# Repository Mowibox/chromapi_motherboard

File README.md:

# chromapi_motherboard

This repo contains a dedicated control HAT designed to manage the high-speed motion, power distribution, and sensor integration required for the quadruped robot [Chromapi](https://github.com/Mowibox/chromapi).

*Designed with KiCad 10.*

## Table of contents

| Section | Description |
| --- | --- |
| [Project overview](#project-overview) | General description of the quadruped control board |
| [Authors](#authors) | Main contributors information |
| [Sponsors & Acknowledgements](#sponsors--acknowledgements) | Information about project sponsors and hardware support |
| [Resources & Documentation](#resources--documentation) | Links to datasheets, BOM, and design architectures |
| [Contributions](#contributions) | How to contribute to the repository |
| [License](#license) | Licensing information |

## Project overview

| Resource | Description | Location | Status |
| :--- | :--- | :--- | :--- |
| **💻 Firmware** | STM32 low-level drivers and communication protocol. | [`/firmware`](./firmware) | **Available** |
| **📐 Schematics** | PDF for hardware architecture | [`/hardware/schematic_pdf`](./hardware/schematic_pdf/chromapi_motherboard_v1.pdf) | **Available** |
| **📦 Manufacturing** | Gerbers, Drill files, BOM, and CPL for assembly. | [`/hardware/production`](./hardware/production/) | **Available** |

### Chromapi's Anatomy

* **🧠 The Brain**: The STM32G431KBT6 MCU handles real-time tasks: servo control, IMU fusion, and power monitoring. The Raspberry Pi runs high-level control, vision, and the Python SDK. They communicate through a custom UART bridge at 2 Mbps.

* **💪 The Muscles**: The SN74LVC1G126 and SN74LVC1G125 buffer the half-duplex TTL serial bus (a single data wire, its direction switched by the USART hardware DE signal) for 12 Feetech STS3215 servos. The STM32 polls servo positions at 200 Hz.

* **❤️ The Heart**: The TPS51388 converts the 18650 2S battery voltage to 5V. The LD39050 generates the 3.3V rail. The INA226 monitors voltage, current, and power via I2C.

* **🛡️ The Immune System**: The CN3302 charges the two 18650 Li-ion cells through USB-C. The HY2120 provides protection against over-discharge, over-current, and short circuits.

* **👁️ The Senses & Balance**: The BMI088 IMU gives acceleration and angular velocity data with SPI. A Mahony filter runs at 400 Hz and outputs orientation as a quaternion. Four foot switches detect ground contact for gait timing.

* **🗣️ The Voice & Expression**: The MAX98357A drives the speaker via I2S communication. The ICS-43434 microphone captures audio through I2S. And the SN74AHCT1G125 level-shifts the 3.3V signal to 5V for the WS2812B RGB LEDs.

## Authors

| |
| :---: |
|  |
| [**Ousmane THIONGANE**](https://mowibox.github.io) |

## Sponsors & Acknowledgements

The hardware development of this board relies on the resources provided by the sponsors below.

### PCBWay

**[PCBWay](https://www.pcbway.com)** is a global manufacturer specializing in rapid prototyping and low-volume hardware production, offering advanced PCB fabrication, turnkey assembly, CNC machining, and 3D printing.

<p align="center">
  
</p>

For this project, I utilized their sponsored [PCB manufacturing](https://www.pcbway.com/orderonline.aspx) and [assembly](https://www.pcbway.fr/pcb-assembly.html) (PCBA) services. Beyond fast production, their engineering team excels at detailed file reviews by cross-checking design options, BOMs, and footprints to prevent errors early. Their reliable component sourcing and rigorous verification were of great help in building a high-quality prototype for Chromapi's motherboard.

---

> Huge thanks to all the hardware folks who reviewed my schematics, or gave me layout tips. I really appreciate your time and support!

## Resources & Documentation

| **⚡ Specifications** | **📄 Bill of Materials** | **📡 Protocol Reference** |
| :---: | :---: | :---: |
| Operating voltages, current limits, and thermal ratings. | Detailed BOM with part numbers and unit costs. | Custom UART protocol between RPi and STM32. |
| 👉 [**View Specs**](https://mowibox.github.io/chroma/en/chromapi/specifications/general/) | 👉 [**View BOM**](https://mowibox.github.io/chroma/en/chromapi/bom/pcb_bom/) | 👉 [**View Protocol**](https://mowibox.github.io/chroma/en/chromapi/documentation/protocol/) |

### Power Architecture

```mermaid
%%{init: {'themeCSS': '.edgeLabel, .edgeLabel p, .labelBkg { background-color: transparent !important; } .edgeLabel rect { fill: transparent !important; }'}}%%
flowchart TD
    CHG[["USB-C charge<br/>CN3302"]] -.->|"charge → B+ ≈ 7.2–8.4V"| CELLS[("Battery<br/>18650 x2")]
    CELLS -->|"B+/BM/B-"| HY["HY2120<br/>BMS protection"]
    HY -->|"B+"| SW[["Power switch"]]

    SW -->|"V_BATT ≈ 7.2–8.4V"| SHUNT[["INA226 shunt sense<br/>2mΩ"]]
    SHUNT -->|"V_SYS ≈ 7.2–8.4V"| REG5{{"Voltage regulation<br/>TPS51388 · Fsw=600kHz"}}
    SHUNT -->|"V_SYS"| SERVOS(["Servomotors x12<br/>Feetech STS3215-C001"])

    REG5 -->|"+5V"| RPI["Raspberry Pi"]
    REG5 -->|"+5V"| FANPWR(["Fan<br/>Noctua NF-A4x10"])
    REG5 -->|"+5V"| LEDPWR(["RGB LEDs<br/>WS2812B"])
    REG5 -->|"+5V"| REG33{{"Voltage regulation<br/>LD39050 LDO"}}

    REG33 -->|"+3.3V"| MCU["MCU<br/>STM32G431KBT6"]
    REG33 -->|"+3.3V"| IMU["IMU<br/>BMI088"]
    REG33 -->|"+3.3V"| INA["Power monitor<br/>INA226"]
    REG33 -->|"+3.3V"| AUDIO["Speaker + Microphone<br/>MAX98357A / ICS-43434"]

    classDef power fill:#dd2757,color:#ffffff,stroke:none
    classDef voltreg fill:#ea684c,color:#ffffff,stroke:none
    classDef ic fill:#25b3ae,color:#ffffff,stroke:none
    classDef actuator fill:#c027e7,color:#ffffff,stroke:none
    classDef sensor fill:#5c5aed,color:#ffffff,stroke:none

    class CHG,CELLS,HY,SW power
    class REG5,REG33 voltreg
    class MCU,RPI,AUDIO ic
    class SERVOS,FANPWR,LEDPWR actuator
    class SHUNT,IMU,INA sensor
```

### Communication Architecture

```mermaid
%%{init: {'themeCSS': '.edgeLabel, .edgeLabel p, .labelBkg { background-color: transparent !important; } .edgeLabel rect { fill: transparent !important; }'}}%%
flowchart LR
    RPI["Raspberry Pi"]
    MCU["STM32G431KBT6<br/>SYSCLK · 160 MHz"]
    SERVOS(["Servomotors x12<br/>STS3215-C001"])
    IMU["IMU<br/>BMI088"]
    PWR["Power Monitor<br/>INA226"]
    LED(["RGB LEDs<br/>WS2812B"])
    CAM["Wide Angle Camera<br/>IMX219-D160"]
    AUDIO["Speaker + Microphone<br/>MAX98357A / ICS-43434"]
    FAN(["Fan<br/>Noctua NF-A4x10"])

    RPI <-->|"Custom bridge protocol<br/>UART1 · 2 Mbps · 100 Hz control loop"| MCU
    MCU <-->|"Half-duplex serial<br/>USART2 · 1 Mbps · 200 Hz"| SERVOS
    MCU <-->|"SPI1 · 5 MHz · 400 Hz (Mahony AHRS)"| IMU
    MCU <-->|"I2C1 · 400 kHz · 10 Hz poll"| PWR
    MCU -->|"PWM+DMA · 800 kHz"| LED

    RPI -->|"CSI-2"| CAM
    RPI <-->|"I2S"| AUDIO
    RPI <-->|"PWM + Tacho"| FAN

    classDef ic fill:#25b3ae,color:#ffffff,stroke:none
    classDef actuator fill:#c027e7,color:#ffffff,stroke:none
    classDef sensor fill:#5c5aed,color:#ffffff,stroke:none

    class RPI,MCU,AUDIO ic
    class SERVOS,LED,FAN actuator
    class IMU,PWR,CAM sensor
```

## Contributions

Contributions are always welcome!

* **Report Issues:** Found an error or have a feature request? Create a new issue [here.](https://github.com/Mowibox/chromapi_motherboard/issues/new/choose)
* **Fix Bugs & Add Features:** Find out where you can lend a hand by checking out [existing issues.](https://github.com/Mowibox/chromapi_motherboard/issues)

## License

This repository is multi-licensed:

| Part | Path | License |
| :--- | :--- | :--- |
| Firmware (own code) | [`/firmware`](./firmware/) | [Apache 2.0](./LICENSE) |
| Hardware (schematics, PCB, footprints, symbols, fabrication files) | [`/hardware`](./hardware/) | [CC BY-NC-SA 4.0](./hardware/LICENSE) |
| Documentation and media (README, images, renders) | [`/assets`](./assets/), this README | [CC BY-NC-SA 4.0](./hardware/LICENSE) |

**Third-party content keeps its own license:** the STM32G4 HAL and CMSIS in [`/firmware/chromapi_stm32_core/Drivers`](./firmware/chromapi_stm32_core/Drivers/) (see their `LICENSE.txt`) and STM32CubeMX-generated files (`main.c`, `stm32g4xx_*`, `syscalls.c`, `sysmem.c`, `system_stm32g4xx.c`, startup and linker files) belong to STMicroelectronics; `ina226.[ch]` is Apache 2.0 by AutoFox; `bmi088.[ch]` is adapted from [pms67/LittleBrain-STM32F4-Sensorboard](https://github.com/pms67/LittleBrain-STM32F4-Sensorboard) and `ws2812b.[ch]` from [hey-frnk/STM32_HAL_NeoPixel](https://github.com/hey-frnk/STM32_HAL_NeoPixel); datasheets in [`/docs`](./docs/) and 3D models in [`/hardware/3d_models`](./hardware/3d_models/) belong to their respective manufacturers; the PCBWay logo (`assets/pcbway.png`) belongs to PCBWay.

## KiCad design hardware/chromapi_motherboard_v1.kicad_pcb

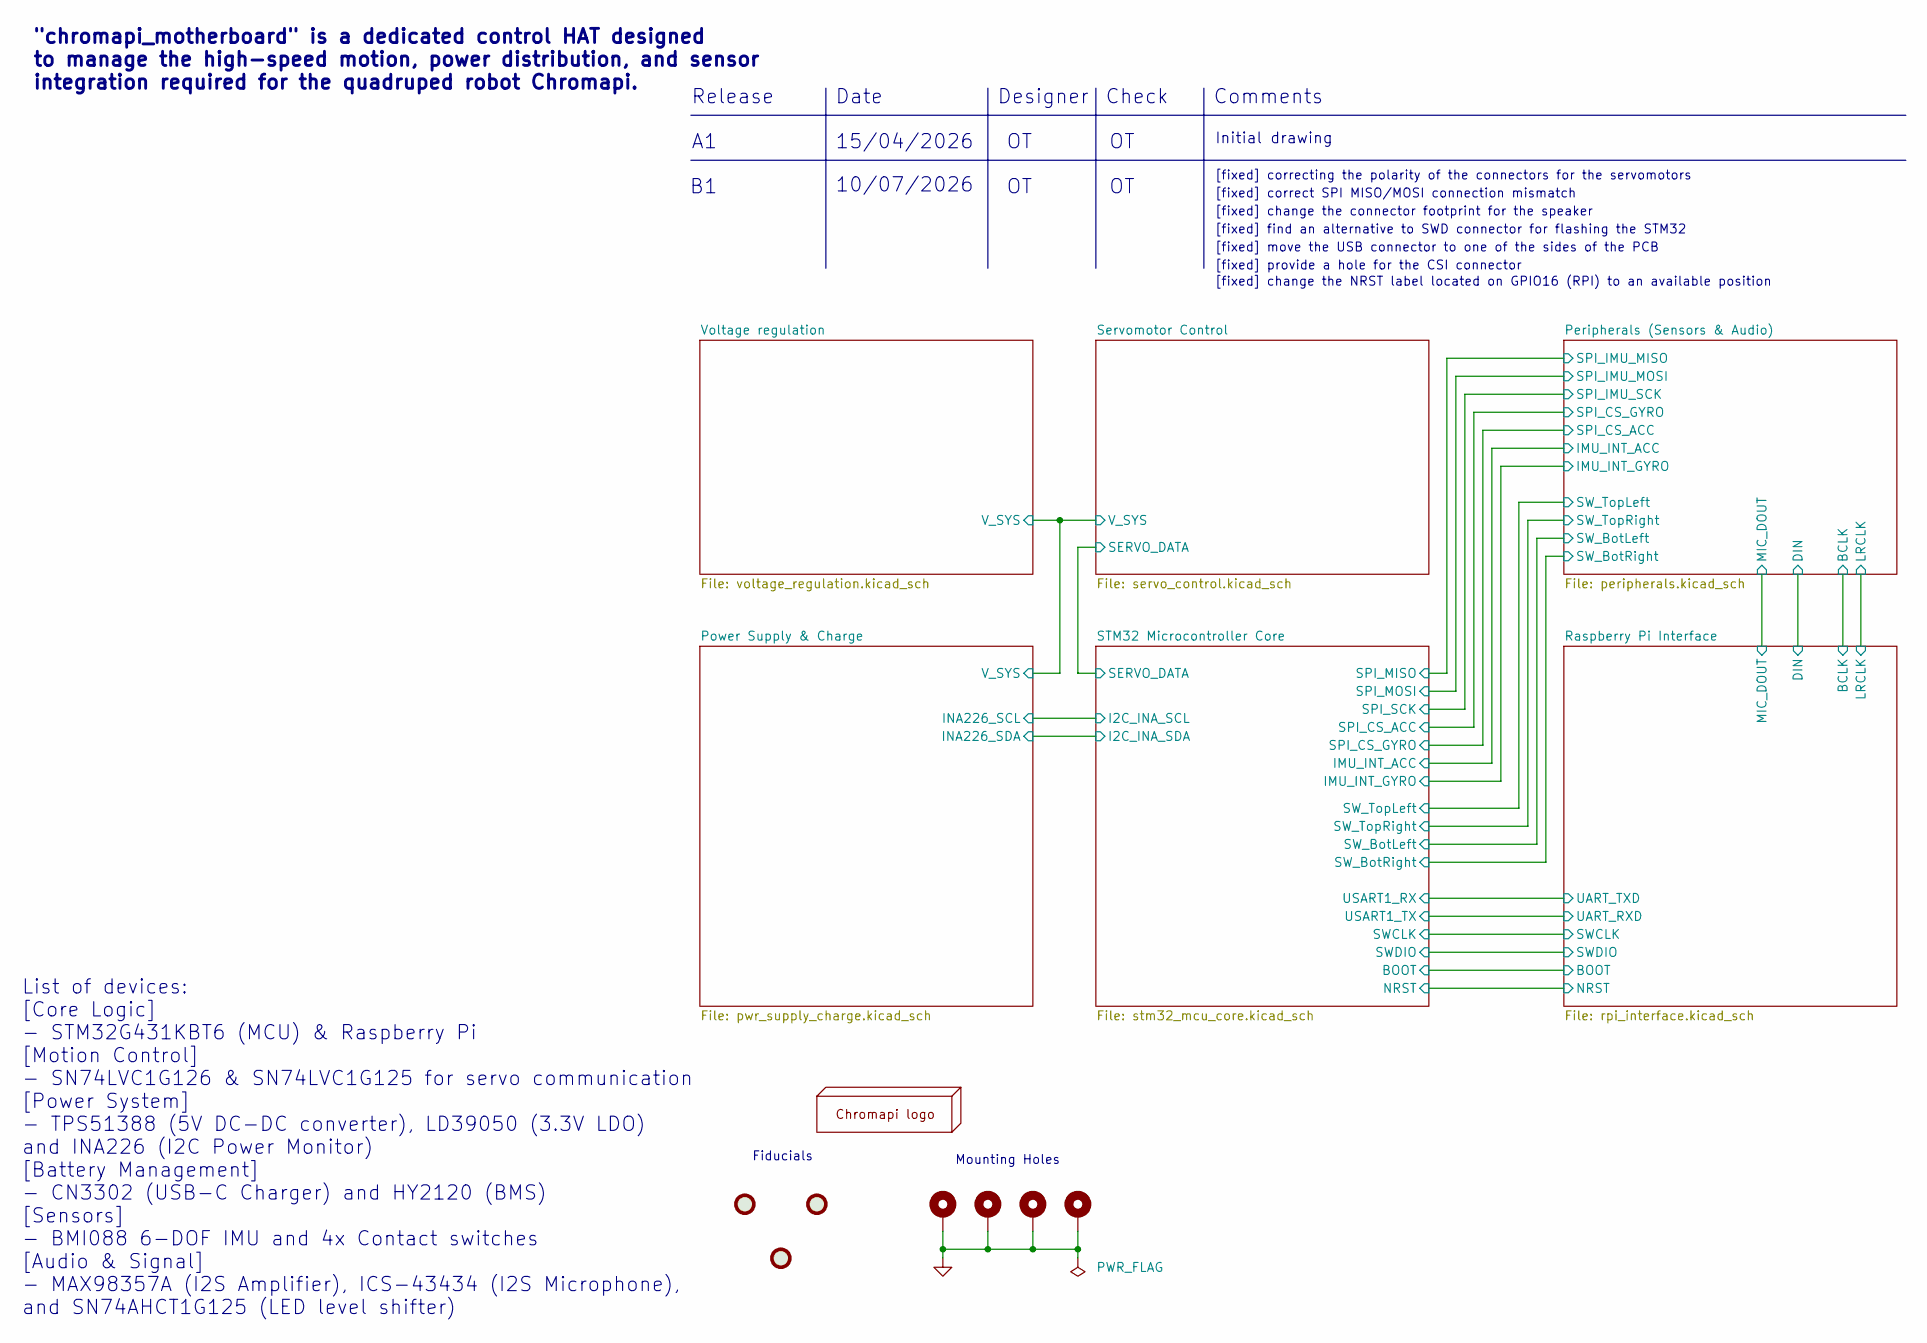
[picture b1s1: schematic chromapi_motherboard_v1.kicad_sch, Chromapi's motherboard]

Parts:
FID1, FID2, FID3: Fiducial; Fiducial_1mm_Mask2mm
H1: chromapi_logo
H2, H3, H4, H5: MountingHole_Pad; MountingHole_2.7mm_M2.5_Pad_Via

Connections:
GND: H2.1 (1_1), H3.1 (1_1), H4.1 (1_1), H5.1 (1_1); also elsewhere on the board

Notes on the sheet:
[fixed] change the connector footprint for the speaker
[fixed] change the NRST label located on GPIO16 (RPI) to an available position
Check
[fixed] correcting the polarity of the connectors for the servomotors
[fixed] provide a hole for the CSI connector
Initial drawing
Release
10/07/2026
[fixed] move the USB connector to one of the sides of the PCB
[fixed] find an alternative to SWD connector for flashing the STM32
"chromapi_motherboard" is a dedicated control HAT designed to manage the high-speed motion, power distribution, and sensor integration required for the quadruped robot Chromapi.
Date
List of devices: [Core Logic] - STM32G431KBT6 (MCU) & Raspberry Pi [Motion Control] - SN74LVC1G126 & SN74LVC1G125 for servo communication [Power System] - TPS51388 (5V DC-DC converter), LD39050 (3.3V LDO) and INA226 (I2C Power Monitor) [Battery Management] - CN3302 (USB-C Charger) and HY2120 (BMS) 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
Fiducials
15/04/2026
Comments
Designer
Mounting Holes
[fixed] correct SPI MISO/MOSI connection mismatch

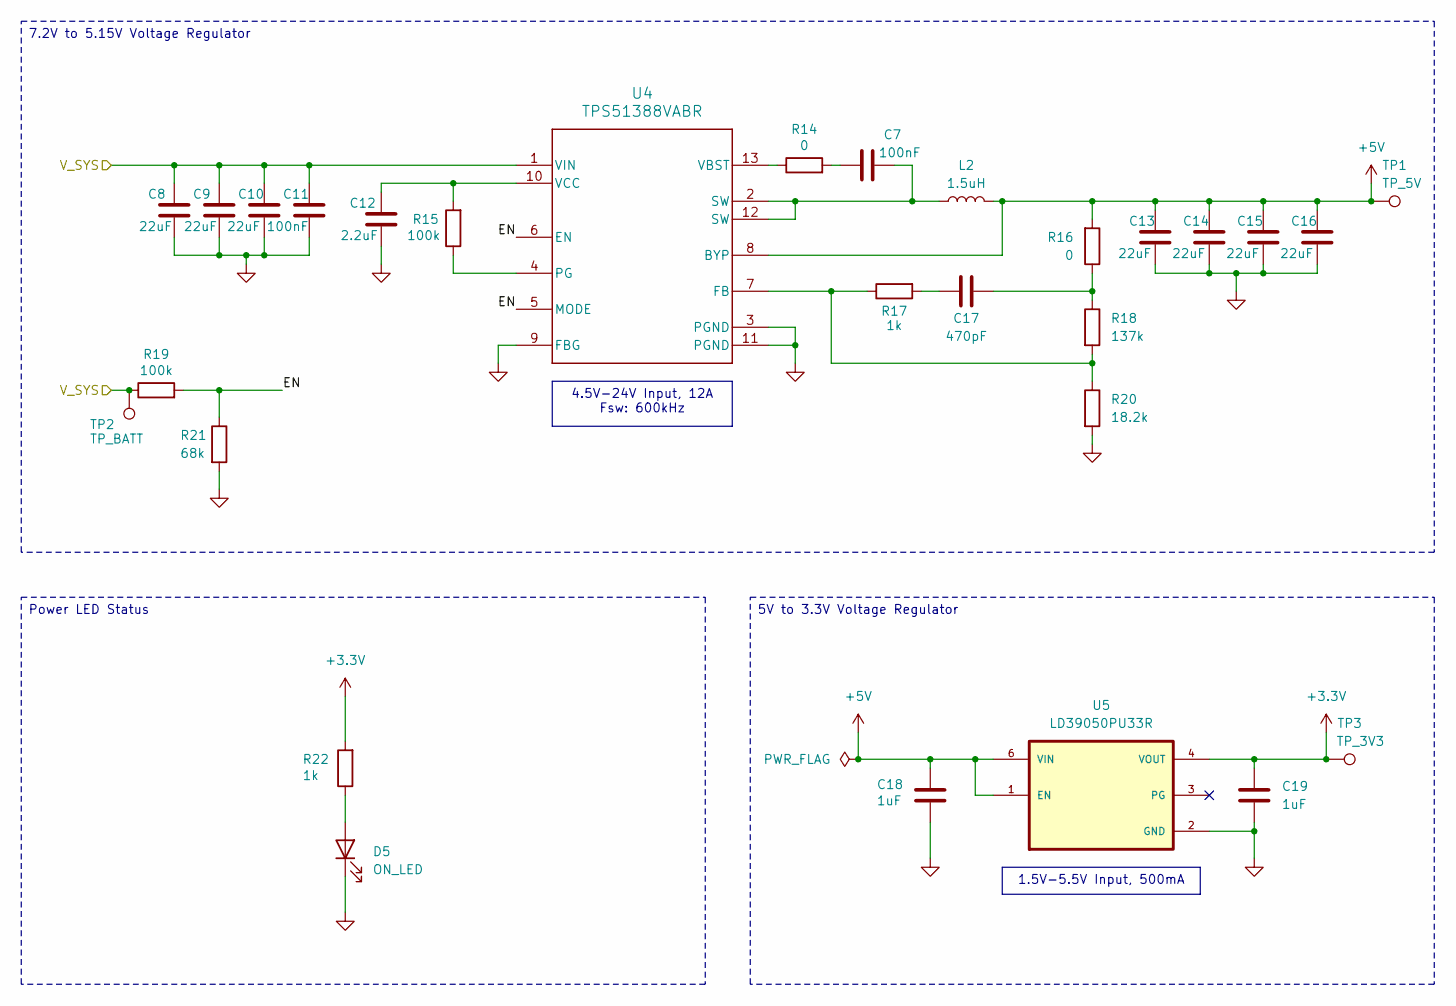
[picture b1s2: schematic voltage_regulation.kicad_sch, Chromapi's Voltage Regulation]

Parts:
C7: 100nF; C_0603_1608Metric; MPN CL10B104KB8NNNC; JLCPCB Part # C14663
C8, C9, C10: 22uF; C_1206_3216Metric; MPN CL31A226KAHNNNE; JLCPCB Part # C12891
C11: 100nF; C_0603_1608Metric; MPN CC0603KRX7R9BB104; JLCPCB Part # C14663
C12: 2.2uF; C_0603_1608Metric; MPN CL10A225KO8NNNC; JLCPCB Part # C23630
C13, C14, C15, C16: 22uF; C_0805_2012Metric; MPN CL21A226MAQNNNE; JLCPCB Part # C45783
C17: 470pF; C_0603_1608Metric; MPN CC0603JRNPO9BN471; JLCPCB Part # C106211
C18, C19: 1uF; C_0603_1608Metric; MPN CL10A105KB8NNNC; JLCPCB Part # C15849
D5: ON_LED; LED_0603_1608Metric; MPN KT-0603B; JLCPCB Part # C2288
L2: 1.5uH; IND_1040-WE-HCI_WRE; MPN 7443552150; JLCPCB Part # C5914133
R14, R16: 0; R_0603_1608Metric; MPN 0603WAF0000T5E; JLCPCB Part # C21189
R15, R19: 100k; R_0603_1608Metric; MPN CRCW0603100KFKEA; JLCPCB Part # C844916
R17, R22: 1k; R_0603_1608Metric; MPN 0603WAF1001T5E; JLCPCB Part # C21190
R18: 137k; R_0603_1608Metric; MPN 0603WAF1373T5E; JLCPCB Part # C22872
R20: 18.2k; R_0603_1608Metric; MPN RC0603FR-0718K2L; JLCPCB Part # C137784
R21: 68k; R_0603_1608Metric; MPN CRCW060368K0FKEA; JLCPCB Part # C844803
TP1: TP_5V; TestPoint_Pad_D1.5mm
TP2: TP_BATT; TestPoint_Pad_D1.5mm
TP3: TP_3V3; TestPoint_Pad_D1.5mm
U4: TPS51388VABR; TPS513885VABR; MPN TPS513885VABR; JLCPCB Part # C41935536
U5: LD39050PU33R; ld39050PU33R_SON95P300X300X100-7N; MPN LD39050PU33R; DIGI-KEY_PART_NUMBER 497-8716-1-ND

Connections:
+3.3V: C19.1, R22.2, TP3.1 (1_1), U5.4 (VOUT); also elsewhere on the board
+5V: C13.1, C14.1, C15.1, C16.1, C18.1, L2.2, R16.2, TP1.1 (1_1), U4.8 (BYP), U5.1 (EN), U5.6 (VIN); also elsewhere on the board
/Power Supply & Charge/V_SYS: C8.1, C9.1, C10.1, C11.1, R19.1, TP2.1 (1_1), U4.1 (VIN); also elsewhere on the board
/Voltage regulation/EN: R19.2, R21.1, U4.5 (MODE), U4.6 (EN)
GND: C8.2, C9.2, C10.2, C11.2, C12.2, C13.2, C14.2, C15.2, C16.2, C18.2, C19.2, D5.1 (K), R20.2, R21.2, U4.3 (PGND), U4.9 (FBG), U4.11 (PGND), U5.2 (GND), U5.7 (GND); also elsewhere on the board
unnamed: C7.1, L2.1, U4.2 (SW), U4.12 (SW)
unnamed: C7.2, R14.2
unnamed: C17.1, R16.1, R18.1
unnamed: C17.2, R17.2
unnamed: D5.2 (A), R22.1
unnamed: R17.1, R18.2, R20.1, U4.7 (FB)
unnamed: R15.1, U4.4 (PG)
unnamed: R14.1, U4.13 (VBST)
unnamed: C12.1, R15.2, U4.10 (VCC)

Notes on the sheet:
Power LED Status
4.5V-24V Input, 12A Fsw: 600kHz
5V to 3.3V Voltage Regulator
1.5V-5.5V Input, 500mA
7.2V to 5.15V Voltage Regulator

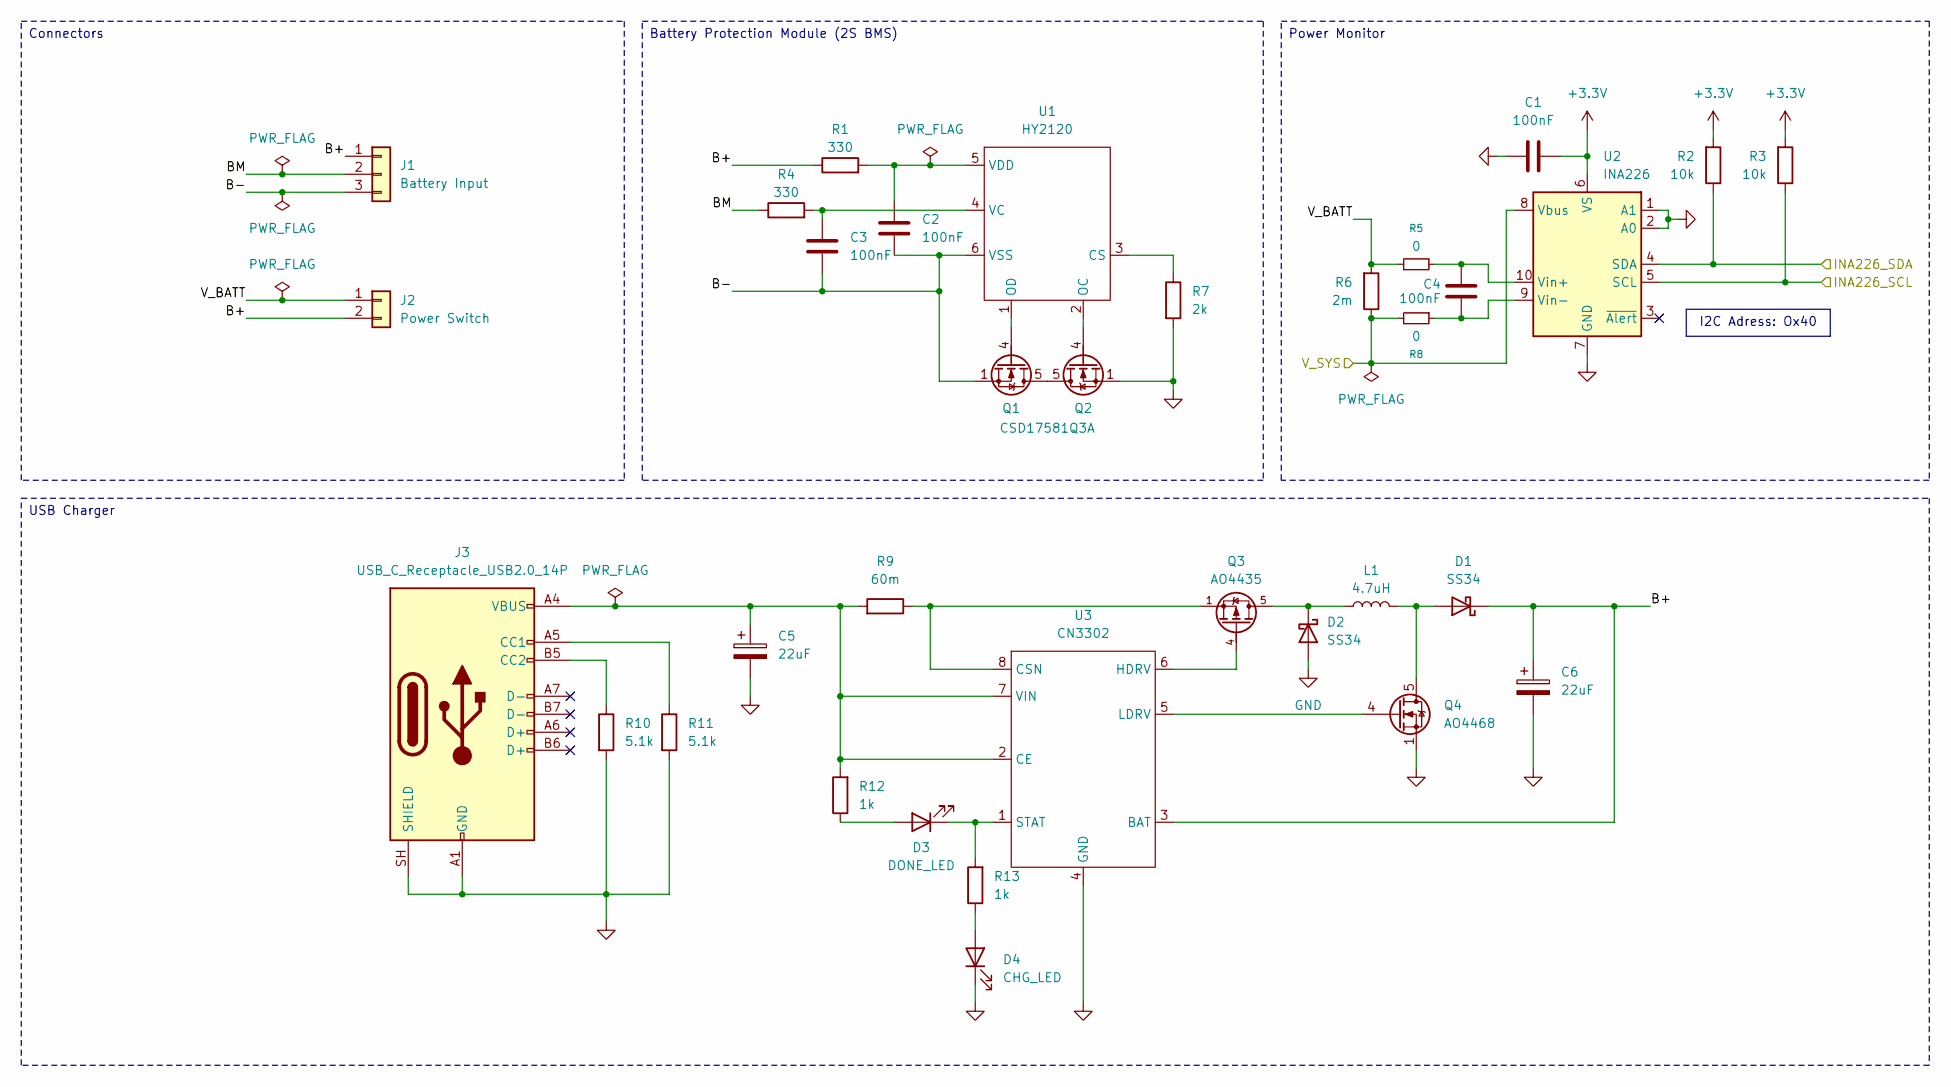
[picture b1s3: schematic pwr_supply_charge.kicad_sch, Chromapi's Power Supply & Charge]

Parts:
C1, C4: 100nF; C_0603_1608Metric; MPN CC0603KRX7R9BB104; JLCPCB Part # C14663
C2, C3: 100nF; C_0402_1005Metric; MPN CL05B104KB54PNC; JLCPCB Part # C307331
C5, C6: 22uF; CP_Elec_5x5.8; MPN EEEHB1C220R; JLCPCB Part # C336501
D1, D2: SS34; D_SMA; MPN SS34; JLCPCB Part # C8678
D3: DONE_LED; LED_0603_1608Metric; MPN KT-0603G; JLCPCB Part # C12624
D4: CHG_LED; LED_0603_1608Metric; MPN KT-0603R; JLCPCB Part # C2286
J1: Battery Input; JST_XH_B3B-XH-A_1x03_P2.50mm_Vertical; MPN B3B-XH-A(LF)(SN); JLCPCB Part # C144394
J2: Power Switch; JST_XH_B2B-XH-A_1x02_P2.50mm_Vertical; MPN B2B-XH-A(LF)(SN); JLCPCB Part # C158012
J3: USB_C_Receptacle_USB2.0_14P; USB_C_Receptacle_HRO_TYPE-C-31-M-12; MPN TYPE-C-31-M-12; JLCPCB Part # C165948
L1: 4.7uH; INDM6864X300N; MPN IHLP2525CZER4R7M01; JLCPCB Part # C553961
Q1, Q2: CSD17581Q3A; VSON-8_3.3x3.3mm_P0.65mm_NexFET; MPN CSD17581Q3A; JLCPCB Part # C2861705
Q3: AO4435; ao4435_SOIC127P600X175-8N; MPN AO4435; JLCPCB Part # C2944310
Q4: AO4468; ao4435_SOIC127P600X175-8N; MPN AO4468; JLCPCB Part # C87410
R1, R4: 330; R_0402_1005Metric; MPN 0402WGF3300TCE; JLCPCB Part # C25104
R2, R3: 10k; R_0402_1005Metric; MPN 0402WGF1002TCE; JLCPCB Part # C25744
R5, R8: 0; R_0603_1608Metric; MPN 0603WAF0000T5E; JLCPCB Part # C21189
R6: 2m; R_2512_6332Metric; MPN HoYLR2512-2W-2mR-1%; JLCPCB Part # C5375414
R7: 2k; R_0402_1005Metric; MPN 0402WGF2001TCE; JLCPCB Part # C4109
R9: 60m; R_1206_3216Metric; MPN RL1206FR-070R06L; JLCPCB Part # C728501
R10, R11: 5.1k; R_0603_1608Metric; MPN 0603WAF5101T5E; JLCPCB Part # C23186
R12, R13: 1k; R_0603_1608Metric; MPN 0603WAF1001T5E; JLCPCB Part # C21190
U1: HY2120; SOT-23-6; MPN HY2120-CB; JLCPCB Part # C116509
U2: INA226; TSSOP-10_3x3mm_P0.5mm; MPN INA226AQDGSRQ1; JLCPCB Part # C2653835
U3: CN3302; SOP-8_3.76x4.96mm_P1.27mm; MPN CN3302; JLCPCB Part # C559039

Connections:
+3.3V: C1.1, R2.2, R3.2, U2.6 (VS); also elsewhere on the board
/Power Supply & Charge/B+: C6.1, D1.1 (K), J1.1, J2.2, R1.1, U3.3 (BAT)
/Power Supply & Charge/B-: C2.2, C3.2, J1.3, Q1.1 (S), Q1.2 (S), Q1.3 (S), U1.6 (VSS)
/Power Supply & Charge/BM: J1.2, R4.1
/Power Supply & Charge/INA226_SCL: R3.1, U2.5 (SCL); also elsewhere on the board
/Power Supply & Charge/INA226_SDA: R2.1, U2.4 (SDA); also elsewhere on the board
/Power Supply & Charge/V_BATT: J2.1, R5.1, R6.2
/Power Supply & Charge/V_SYS: R6.1, R8.2, U2.8 (Vbus); also elsewhere on the board
GND: C1.2, C5.2, C6.2, D2.2 (A), D4.1 (K), J3.A1 (GND), J3.A12 (GND), J3.B1 (GND), J3.B12 (GND), J3.SH (SHIELD), Q2.1 (S), Q2.2 (S), Q2.3 (S), Q4.1 (S), Q4.2 (S), Q4.3 (S), R7.2, R10.2, R11.2, U2.1 (A1), U2.2 (A0), U2.7 (GND), U3.4 (GND); also elsewhere on the board
unnamed: D1.2 (A), L1.2, Q4.5 (D), Q4.6 (D), Q4.7 (D), Q4.8 (D)
unnamed: D2.1 (K), L1.1, Q3.5, Q3.6, Q3.7, Q3.8
unnamed: D3.2 (A), R12.1
unnamed: D3.1 (K), R13.2, U3.1 (STAT)
unnamed: D4.2 (A), R13.1
unnamed: J3.A5 (CC1), R11.1
unnamed: J3.B5 (CC2), R10.1
unnamed: Q1.5 (D), Q2.5 (D)
unnamed: Q1.4 (G), U1.1 (OD)
unnamed: Q2.4 (G), U1.2 (OC)
unnamed: Q4.4 (G), U3.5 (LDRV)
unnamed: R7.1, U1.3 (CS)
unnamed: C3.1, R4.2, U1.4 (VC)
unnamed: C2.1, R1.2, U1.5 (VDD)
unnamed: C4.1, R5.2, U2.10 (Vin+)
unnamed: C4.2, R8.1, U2.9 (Vin-)
unnamed: C5.1, J3.A4 (VBUS), J3.A9 (VBUS), J3.B4 (VBUS), J3.B9 (VBUS), R9.2, R12.2, U3.2 (CE), U3.7 (VIN)
unnamed: Q3.1, Q3.2, Q3.3, R9.1, U3.8 (CSN)
unnamed: Q3.4, U3.6 (HDRV)

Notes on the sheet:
USB Charger
Connectors
I2C Adress: Ox40
Battery Protection Module (2S BMS)
Power Monitor

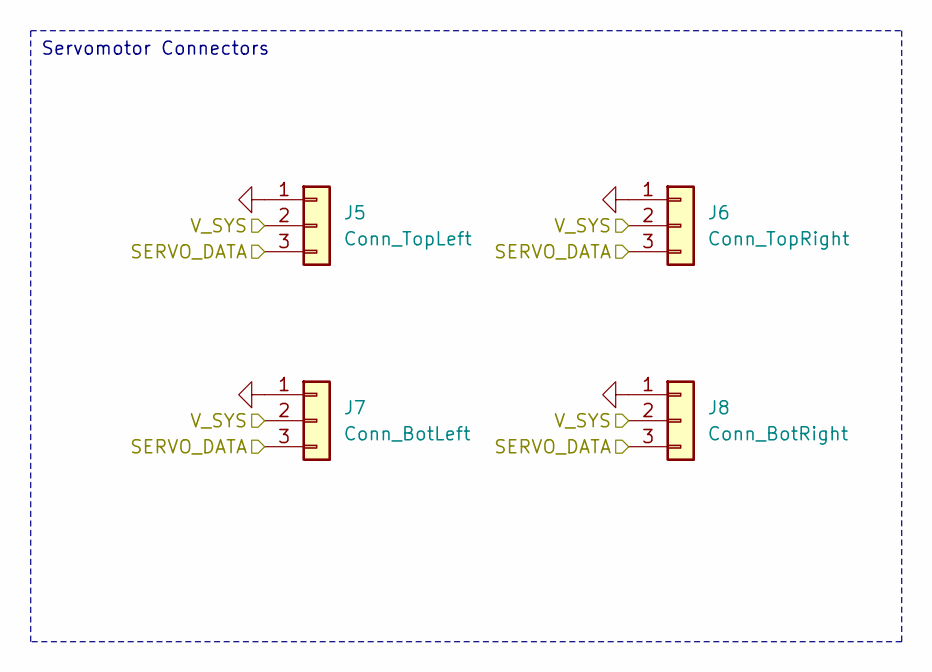
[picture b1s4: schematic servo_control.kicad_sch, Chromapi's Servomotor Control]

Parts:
J5: Conn_TopLeft; Molex_SPOX_5267-03A_1x03_P2.50mm_Vertical; MPN 5267-03A
J6: Conn_TopRight; Molex_SPOX_5267-03A_1x03_P2.50mm_Vertical; MPN 5267-03A
J7: Conn_BotLeft; Molex_SPOX_5267-03A_1x03_P2.50mm_Vertical; MPN 5267-03A
J8: Conn_BotRight; Molex_SPOX_5267-03A_1x03_P2.50mm_Vertical; MPN 5267-03A

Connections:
/Power Supply & Charge/V_SYS: J5.2, J6.2, J7.2, J8.2; also elsewhere on the board
/STM32 Microcontroller Core/SERVO_DATA: J5.3, J6.3, J7.3, J8.3; also elsewhere on the board
GND: J5.1, J6.1, J7.1, J8.1; also elsewhere on the board

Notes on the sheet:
Servomotor Connectors

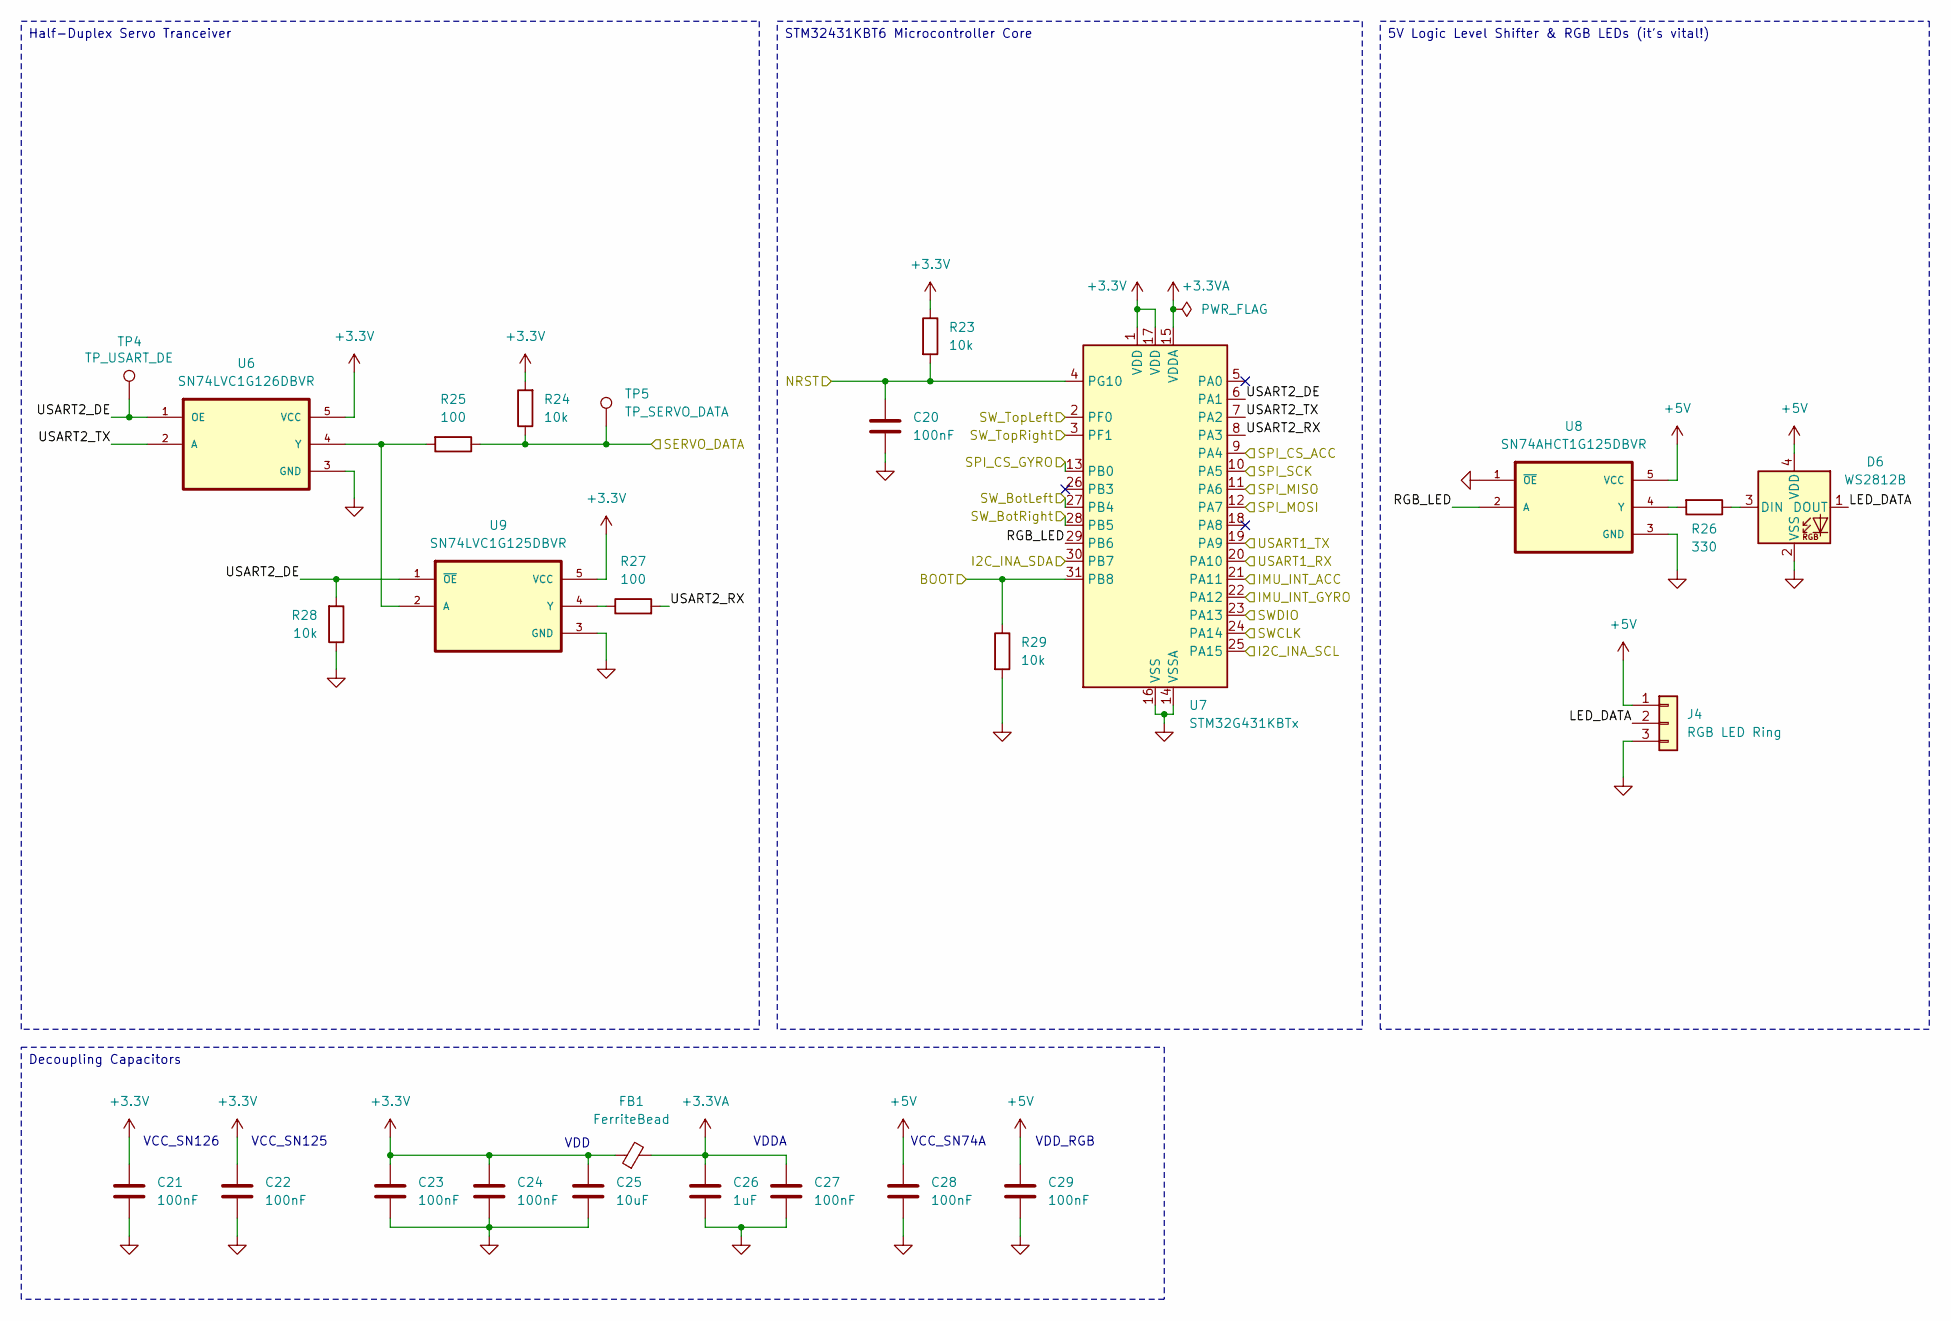
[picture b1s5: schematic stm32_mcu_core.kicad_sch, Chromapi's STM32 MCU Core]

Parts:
C20, C21, C22, C23, C24, C27, C28, C29: 100nF; C_0402_1005Metric; MPN CL05B104KB54PNC; JLCPCB Part # C307331
C25: 10uF; C_0805_2012Metric; MPN CL21A106KAYNNNE; JLCPCB Part # C15850
C26: 1uF; C_0603_1608Metric; MPN CL10A105KB8NNNC; JLCPCB Part # C15849
D6: WS2812B; LED_WS2812B-2020_PLCC4_2.0x2.0mm; MPN WS2812B-2020; JLCPCB Part # C965555
FB1: FerriteBead; L_0805_2012Metric; MPN MPZ2012S331AT000; JLCPCB Part # C76819
J4: RGB LED Ring; JST_XH_B3B-XH-A_1x03_P2.50mm_Vertical; MPN B3B-XH-A(LF)(SN); JLCPCB Part # C144394
R23, R24, R28, R29: 10k; R_0402_1005Metric; MPN 0402WGF1002TCE; JLCPCB Part # C25744
R25, R27: 100; R_0402_1005Metric; MPN 0402WGF1000TCE; JLCPCB Part # C25076
R26: 330; R_0402_1005Metric; MPN 0402WGF3300TCE; JLCPCB Part # C25104
TP4: TP_USART_DE; TestPoint_Pad_D1.0mm
TP5: TP_SERVO_DATA; TestPoint_Pad_D1.0mm
U6: SN74LVC1G126DBVR; SOT95P280X145-5N; MPN SN74LVC1G126DBVR; JLCPCB Part # C7834
U7: STM32G431KBTx; LQFP-32_7x7mm_P0.8mm; MPN STM32G431KBT6; JLCPCB Part # C529357
U8: SN74AHCT1G125DBVR; SOT95P280X145-5N; MPN SN74AHCT1G125DBVR; JLCPCB Part # C7484
U9: SN74LVC1G125DBVR; SOT95P280X145-5N; MPN SN74LVC1G125DBVR; JLCPCB Part # C23654

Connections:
+3.3V: C21.1, C22.1, C23.1, C24.1, C25.1, FB1.1, R23.1, R24.2, U6.5 (VCC), U7.1 (VDD), U7.17 (VDD), U9.5 (VCC); also elsewhere on the board
+3.3VA: C26.1, C27.1, FB1.2, U7.15 (VDDA)
+5V: C28.1, C29.1, D6.4 (VDD), J4.1, U8.5 (VCC); also elsewhere on the board
/Peripherals (Sensors & Audio)/IMU_INT_ACC: U7.21 (PA11); also elsewhere on the board
/Peripherals (Sensors & Audio)/IMU_INT_GYRO: U7.22 (PA12); also elsewhere on the board
/Peripherals (Sensors & Audio)/SPI_CS_ACC: U7.13 (PB0); also elsewhere on the board
/Peripherals (Sensors & Audio)/SPI_CS_GYRO: U7.9 (PA4); also elsewhere on the board
/Peripherals (Sensors & Audio)/SPI_IMU_MISO: U7.11 (PA6); also elsewhere on the board
/Peripherals (Sensors & Audio)/SPI_IMU_MOSI: U7.12 (PA7); also elsewhere on the board
/Peripherals (Sensors & Audio)/SPI_IMU_SCK: U7.10 (PA5); also elsewhere on the board
/Peripherals (Sensors & Audio)/SW_BotLeft: U7.27 (PB4); also elsewhere on the board
/Peripherals (Sensors & Audio)/SW_BotRight: U7.28 (PB5); also elsewhere on the board
/Peripherals (Sensors & Audio)/SW_TopLeft: U7.2 (PF0); also elsewhere on the board
/Peripherals (Sensors & Audio)/SW_TopRight: U7.3 (PF1); also elsewhere on the board
/Power Supply & Charge/INA226_SCL: U7.25 (PA15); also elsewhere on the board
/Power Supply & Charge/INA226_SDA: U7.30 (PB7); also elsewhere on the board
/Raspberry Pi Interface/BOOT: R29.1, U7.31 (PB8); also elsewhere on the board
/Raspberry Pi Interface/NRST: C20.1, R23.2, U7.4 (PG10); also elsewhere on the board
/Raspberry Pi Interface/SWCLK: U7.24 (PA14); also elsewhere on the board
/Raspberry Pi Interface/SWDIO: U7.23 (PA13); also elsewhere on the board
/Raspberry Pi Interface/UART_RXD: U7.19 (PA9); also elsewhere on the board
/Raspberry Pi Interface/UART_TXD: U7.20 (PA10); also elsewhere on the board
/STM32 Microcontroller Core/LED_DATA: D6.1 (DOUT), J4.2
/STM32 Microcontroller Core/RGB_LED: U7.29 (PB6), U8.2 (A)
/STM32 Microcontroller Core/SERVO_DATA: R24.1, R25.1, TP5.1 (1_1); also elsewhere on the board
/STM32 Microcontroller Core/USART2_DE: R28.2, TP4.1 (1_1), U6.1 (OE), U7.6 (PA1), U9.1 (~OE)
/STM32 Microcontroller Core/USART2_RX: R27.2, U7.8 (PA3)
/STM32 Microcontroller Core/USART2_TX: U6.2 (A), U7.7 (PA2)
GND: C20.2, C21.2, C22.2, C23.2, C24.2, C25.2, C26.2, C27.2, C28.2, C29.2, D6.2 (VSS), J4.3, R28.1, R29.2, U6.3 (GND), U7.14 (VSSA), U7.16 (VSS), U7.32 (VSS), U8.1 (~OE), U8.3 (GND), U9.3 (GND); also elsewhere on the board
unnamed: D6.3 (DIN), R26.1
unnamed: R25.2, U6.4 (Y), U9.2 (A)
unnamed: R26.2, U8.4 (Y)
unnamed: R27.1, U9.4 (Y)

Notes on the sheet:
VCC_SN74A
VDD
VCC_SN126
VDD_RGB
VCC_SN125
VDDA
STM32431KBT6 Microcontroller Core
5V Logic Level Shifter & RGB LEDs (it's vital!)
Half-Duplex Servo Tranceiver
Decoupling Capacitors
